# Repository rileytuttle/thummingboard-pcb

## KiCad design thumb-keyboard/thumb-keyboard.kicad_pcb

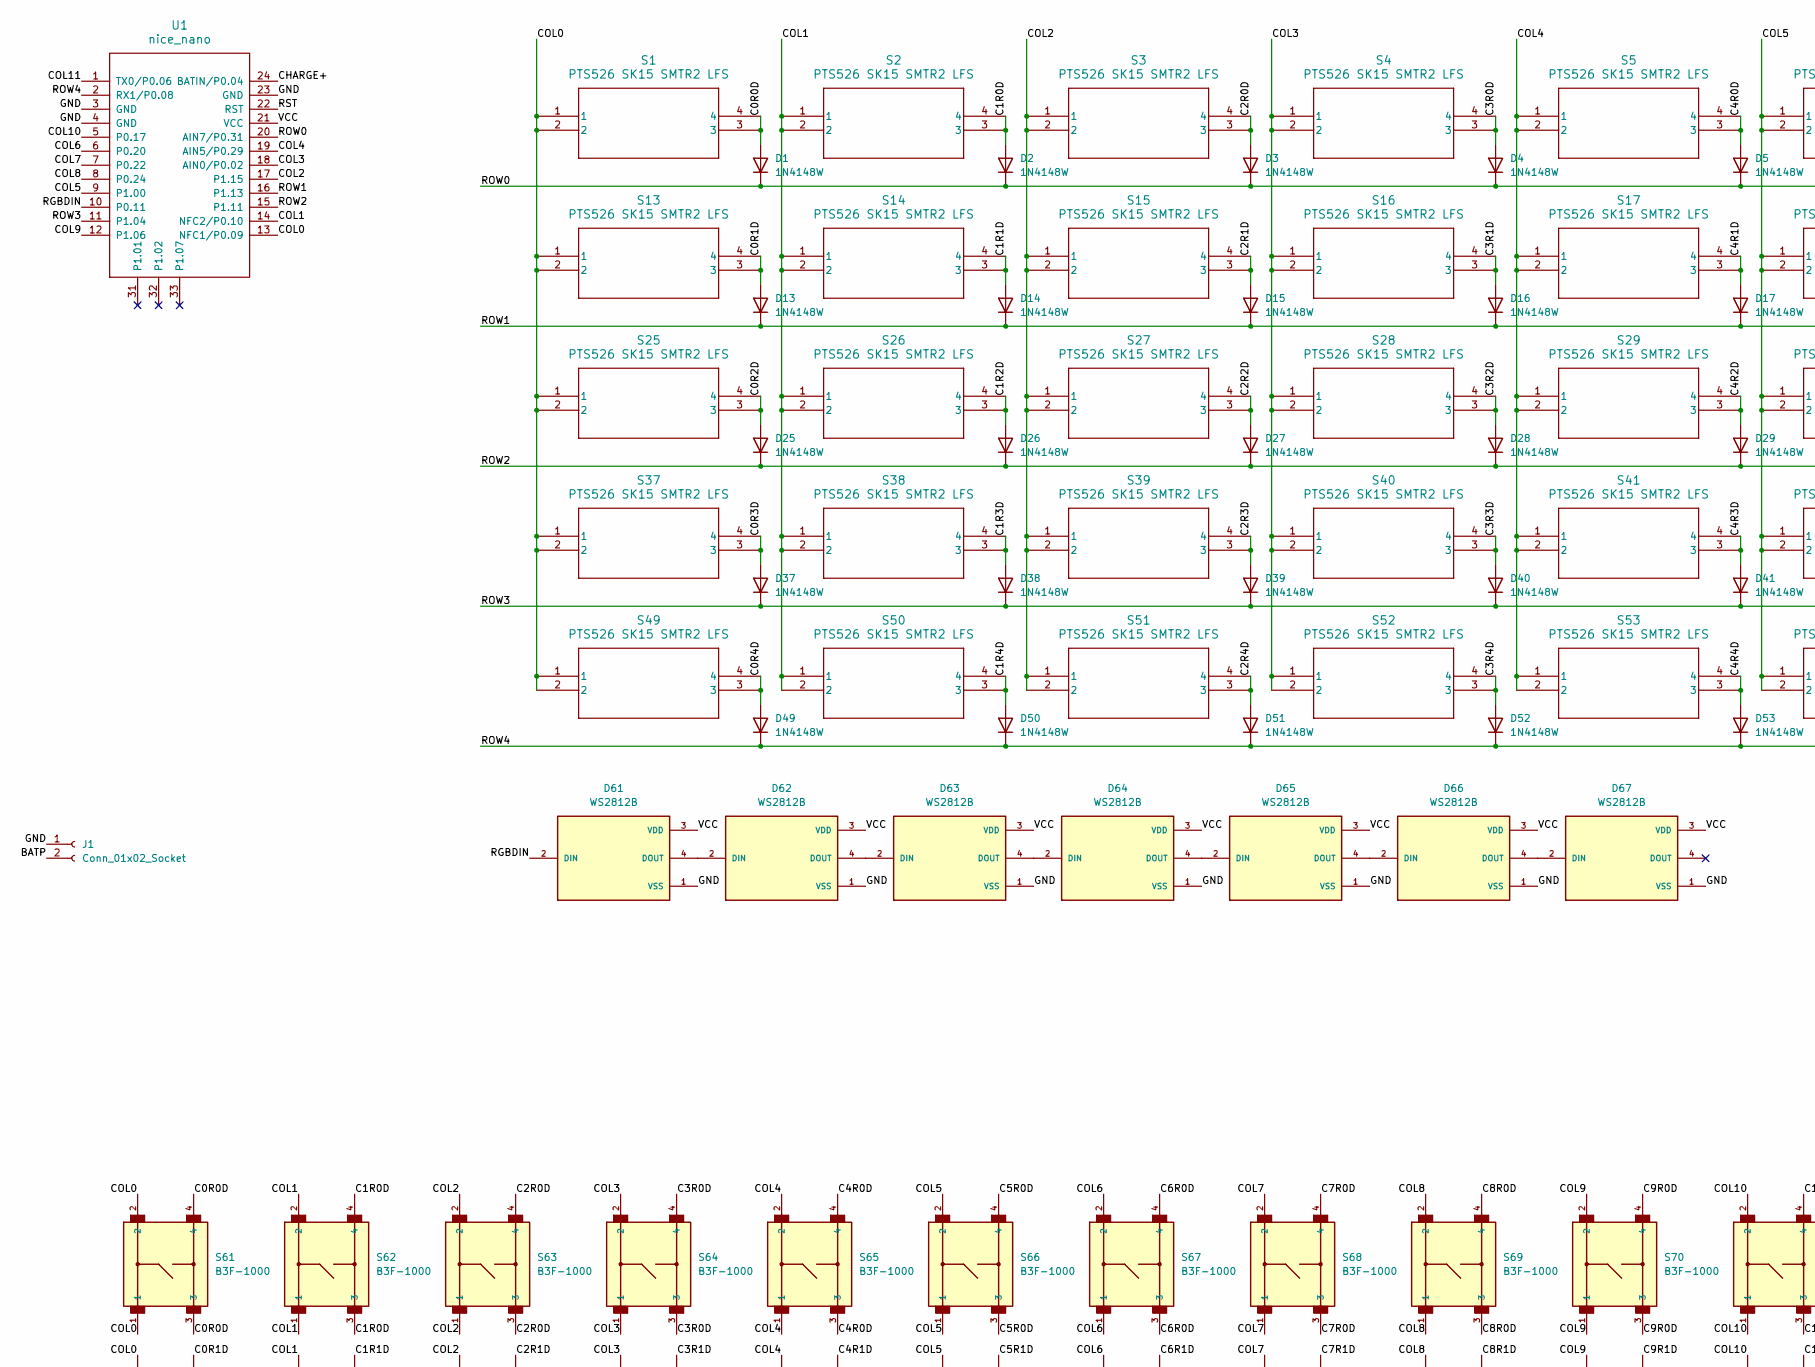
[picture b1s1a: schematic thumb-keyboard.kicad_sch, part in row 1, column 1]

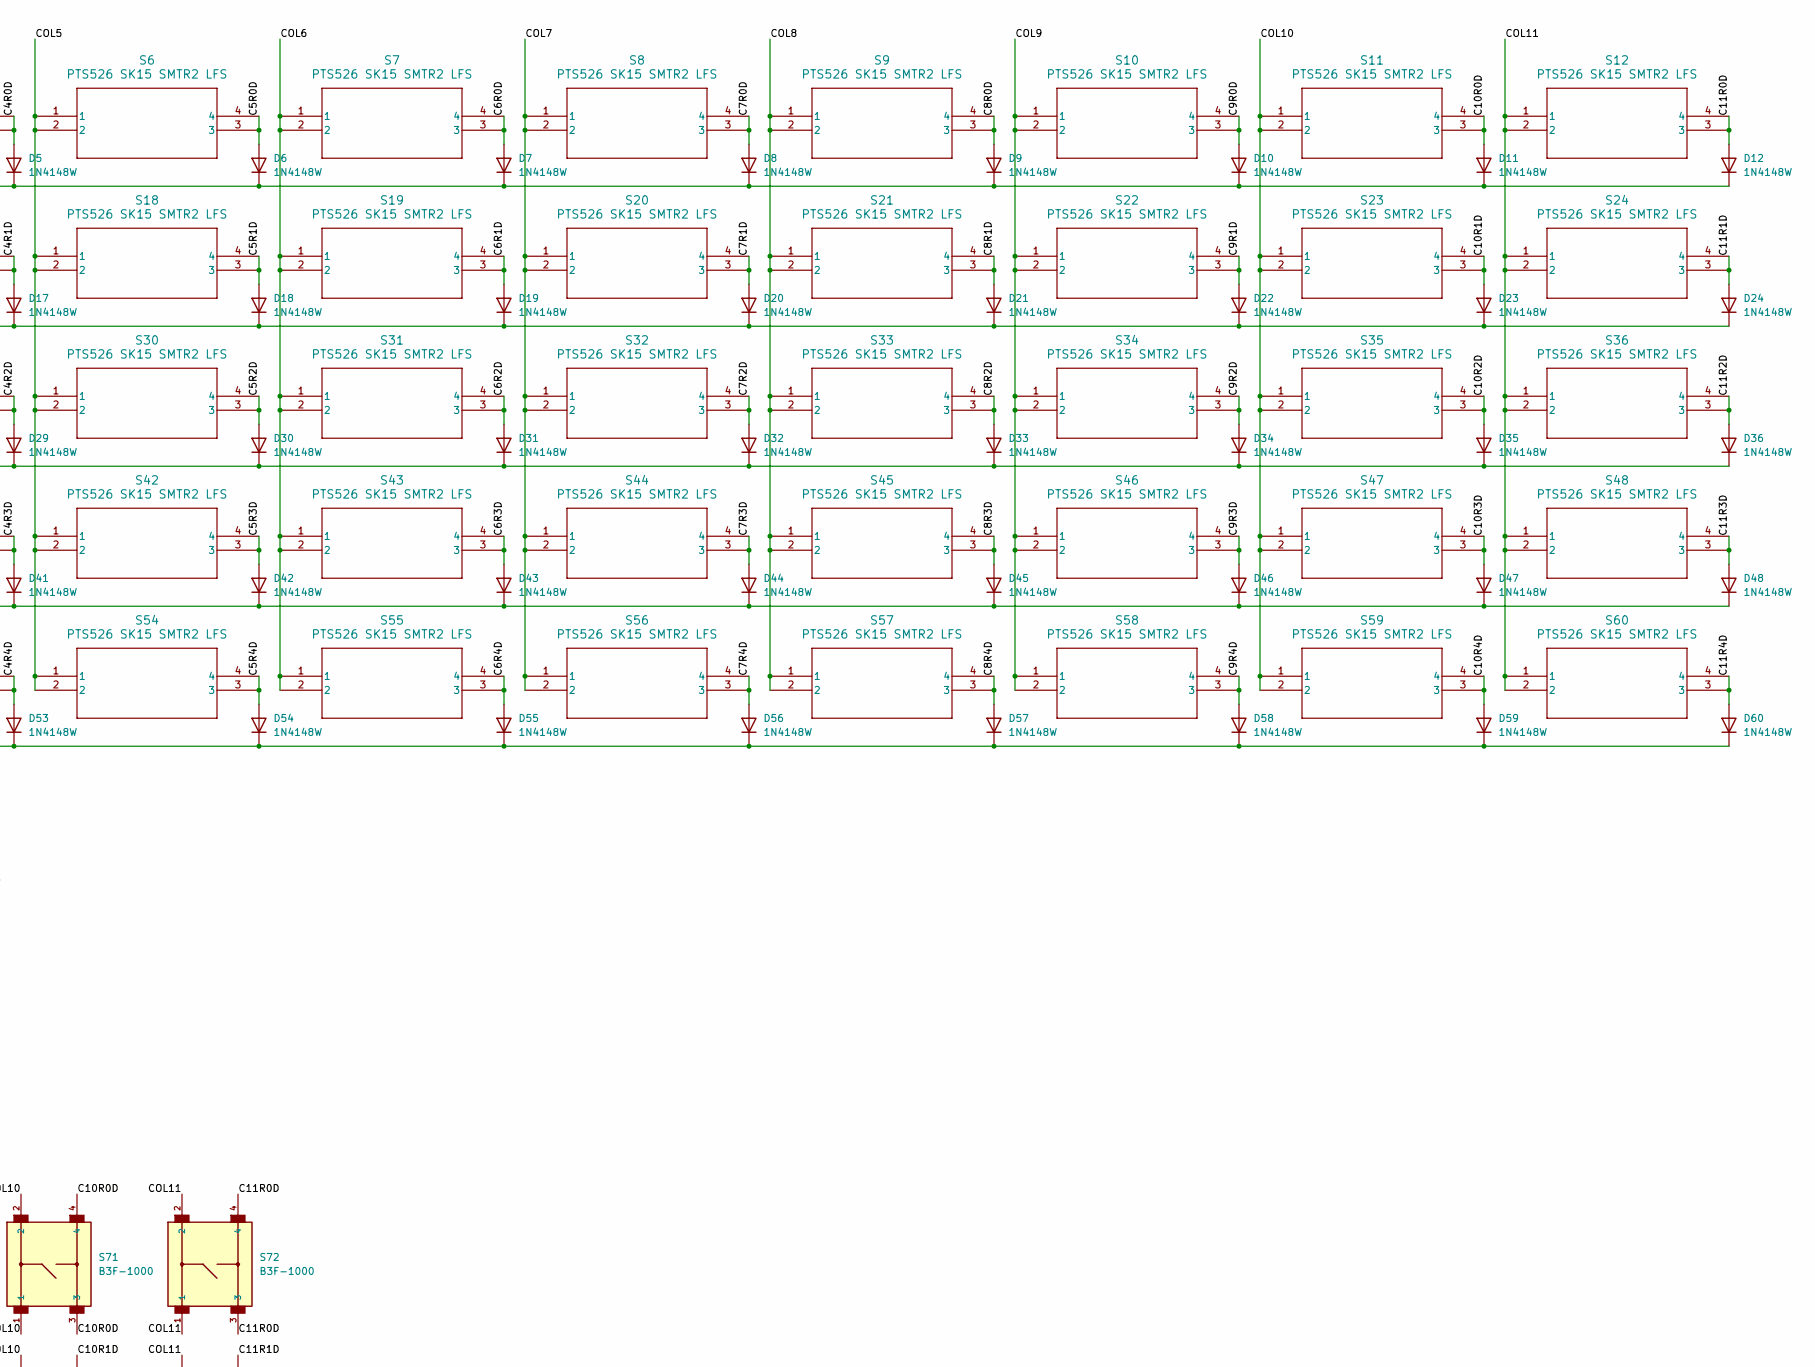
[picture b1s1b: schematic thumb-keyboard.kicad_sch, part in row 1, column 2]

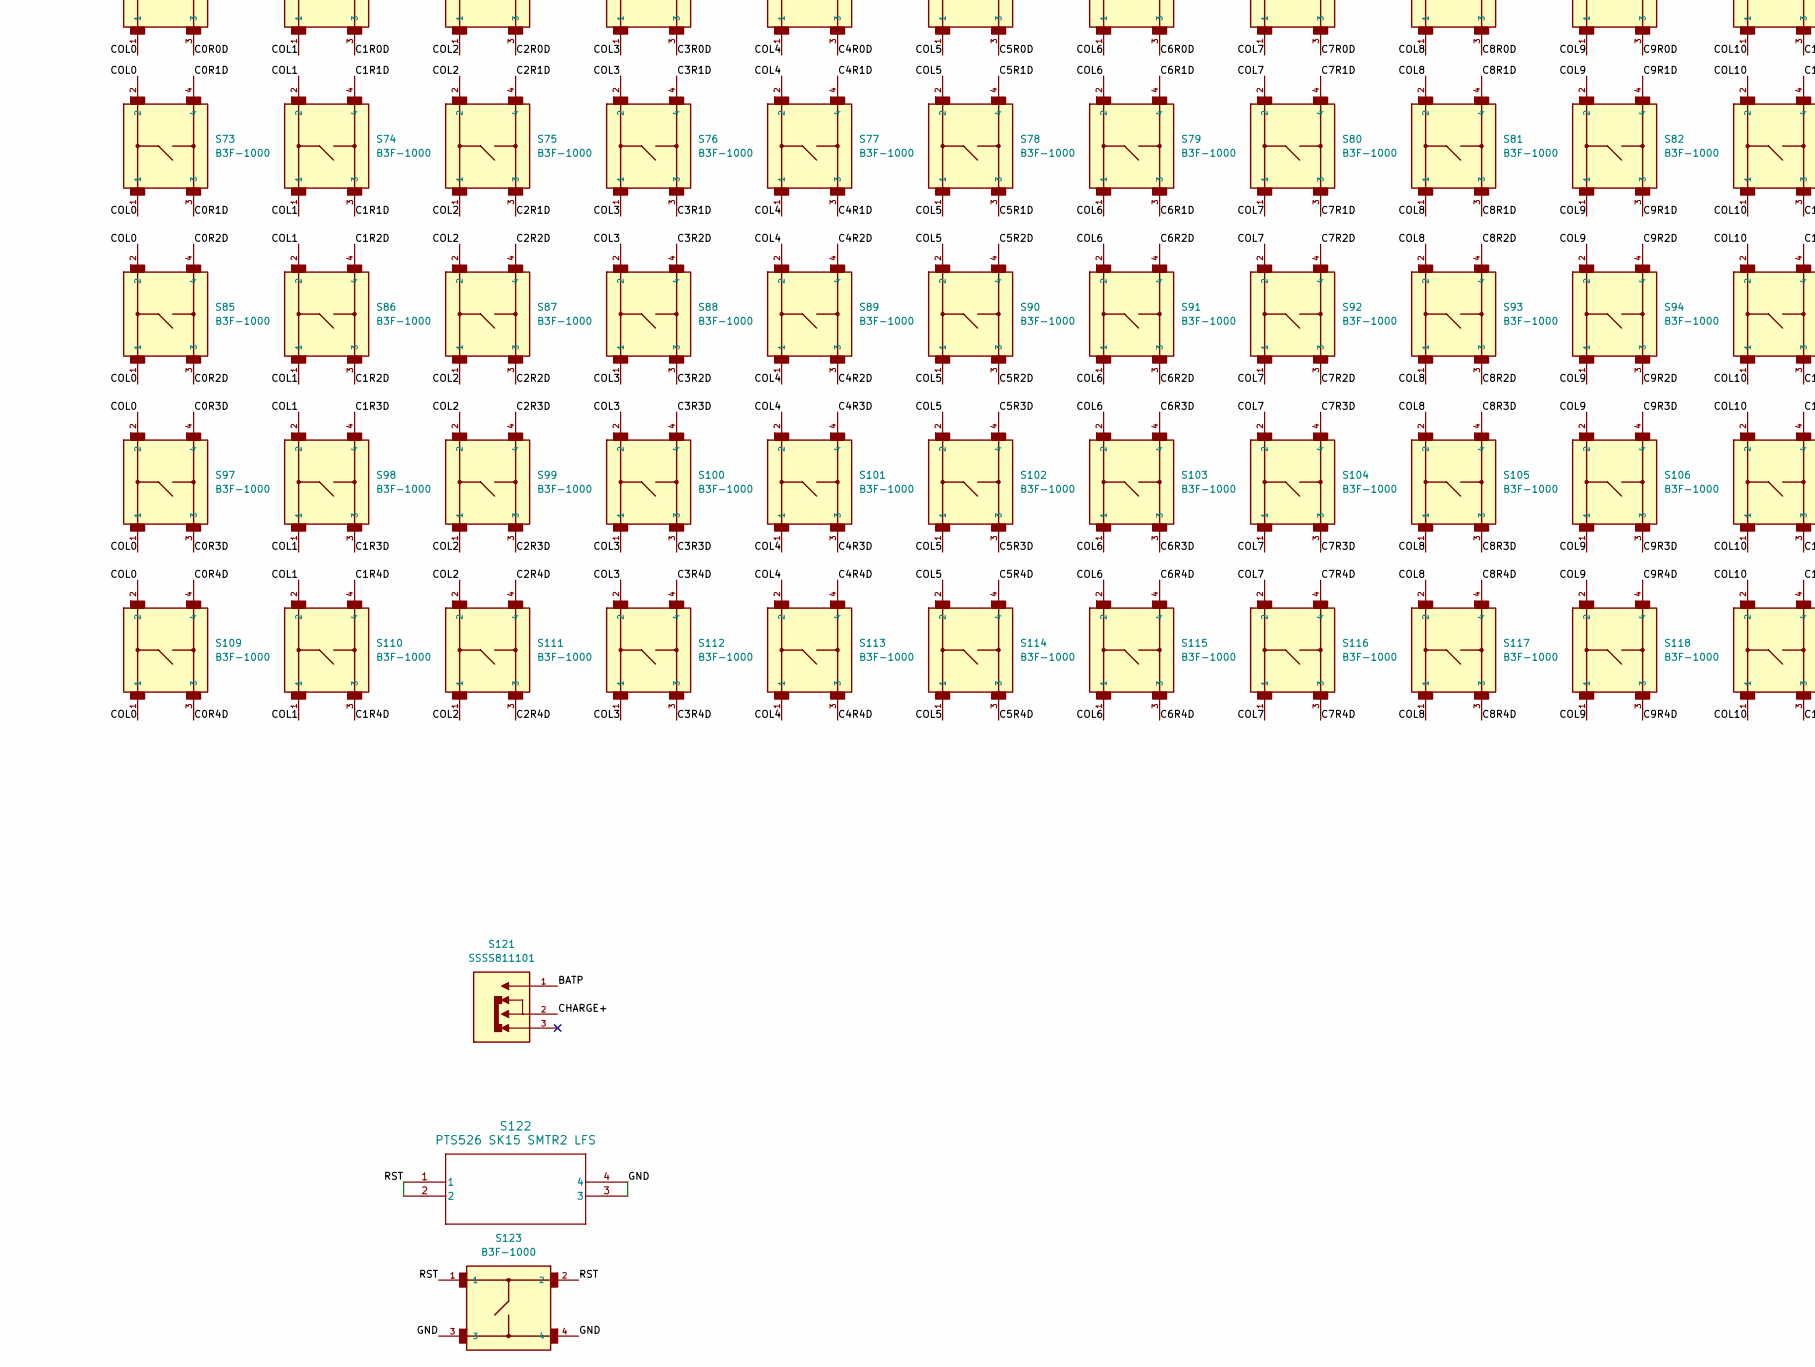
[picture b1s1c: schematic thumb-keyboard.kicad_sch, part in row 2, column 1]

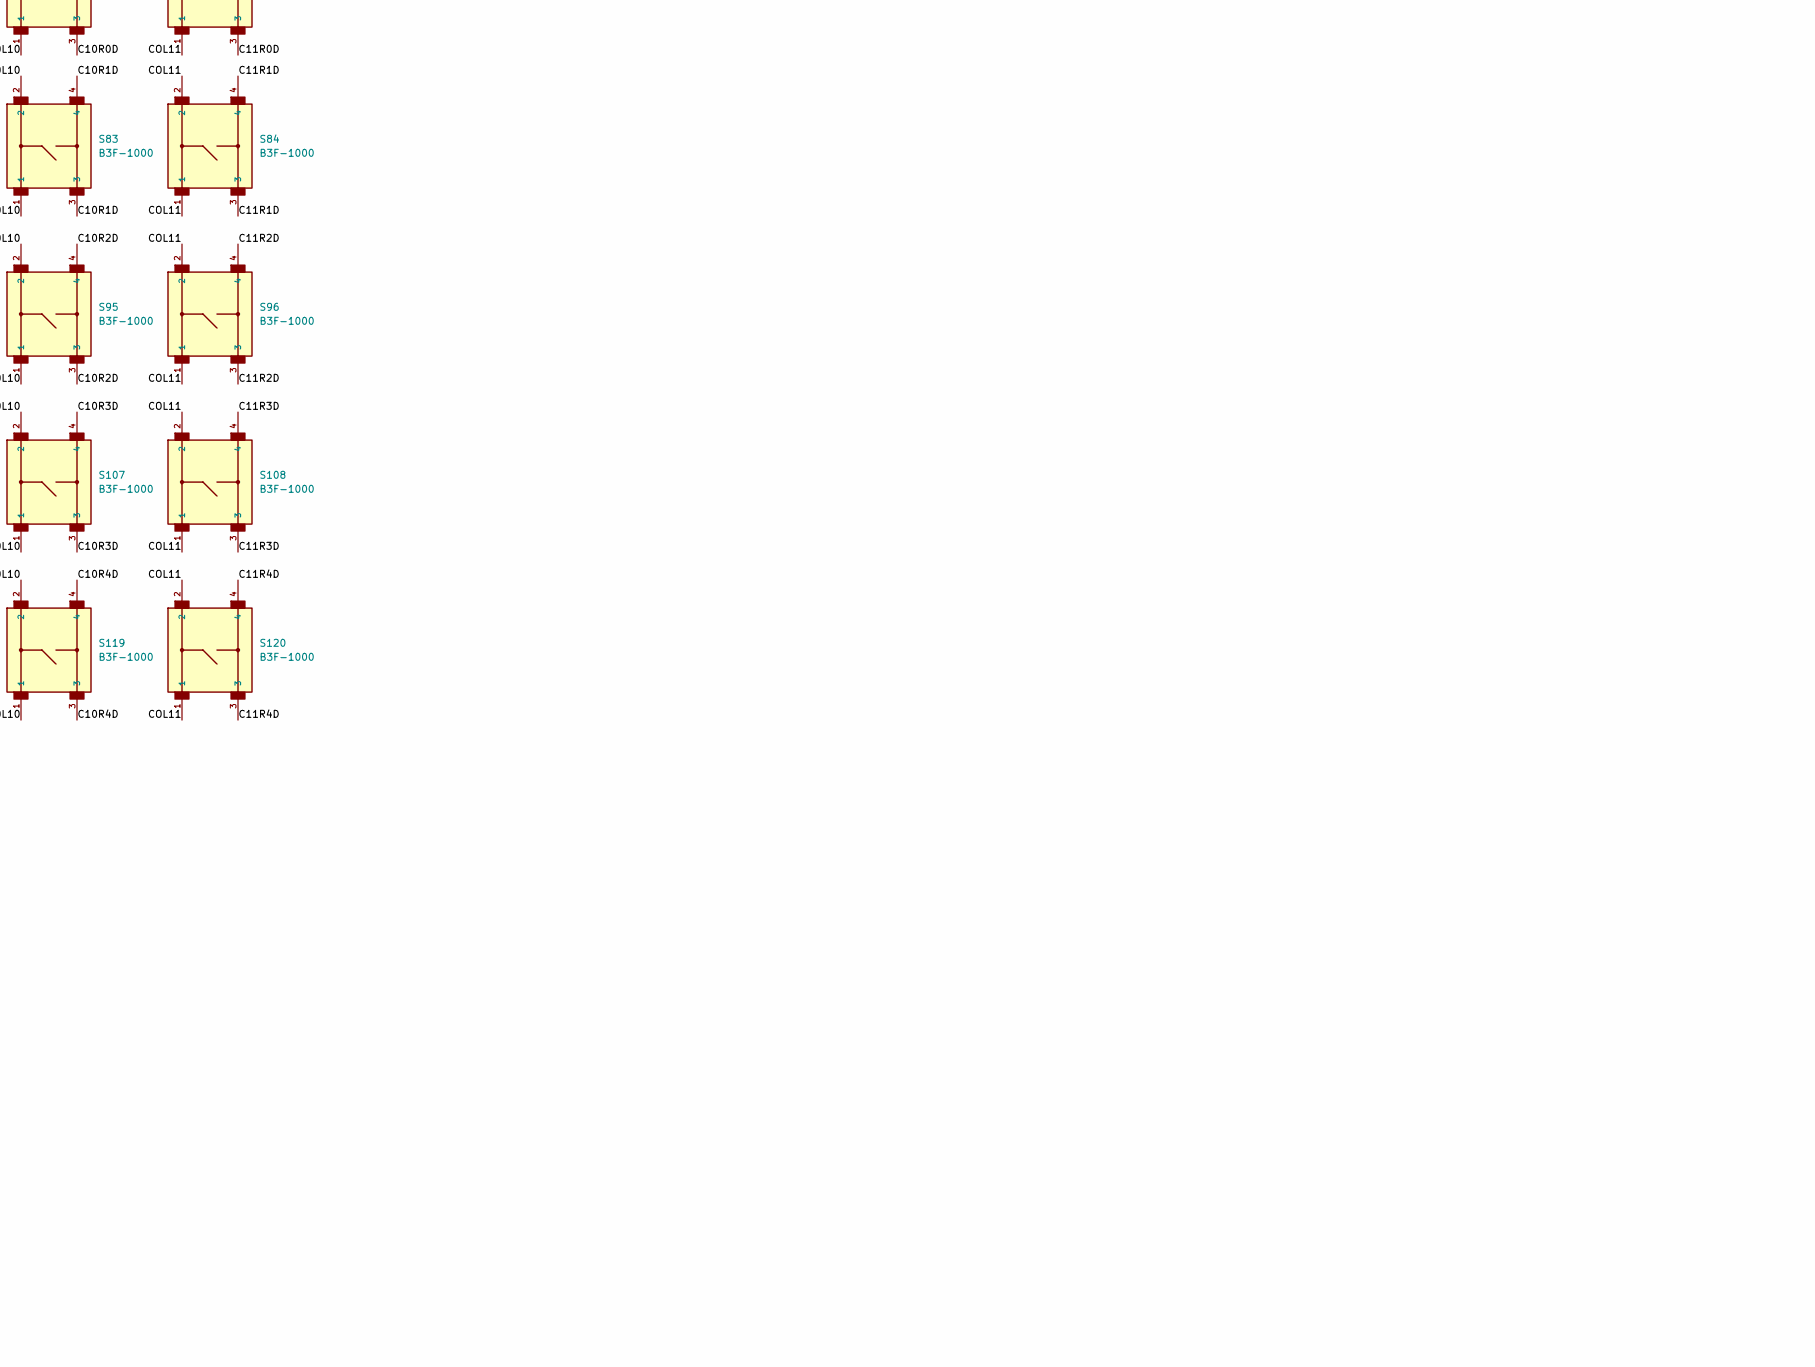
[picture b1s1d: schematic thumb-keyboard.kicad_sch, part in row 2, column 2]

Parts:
D1, D2, D3, D4, D5, D6, D7, D8, D9, D10, D11, D12, D13, D14, D15, D16, D17, D18, D19, D20, D21, D22, D23, D24, D25, D26, D27, D28, D29, D30, D31, D32, D33, D34, D35, D36, D37, D38, D39, D40, D41, D42, D43, D44, D45, D46, D47, D48, D49, D50, D51, D52, D53, D54, D55, D56, D57, D58, D59, D60: 1N4148W; D_SOD-123
D61, D62, D63, D64, D65, D66, D67: WS2812B; LED_1655; PARTREV 01
J1: Conn_01x02_Socket; JST_PH_S2B-PH-K_1x02_P2.00mm_Horizontal
S1, S2, S3, S4, S5, S6, S7, S8, S9, S10, S11, S12, S13, S14, S15, S16, S17, S18, S19, S20, S21, S22, S23, S24, S25, S26, S27, S28, S29, S30, S31, S32, S33, S34, S35, S36, S37, S38, S39, S40, S41, S42, S43, S44, S45, S46, S47, S48, S49, S50, S51, S52, S53, S54, S55, S56, S57, S58, S59, S60, S122: PTS526 SK15 SMTR2 LFS; SMT_FS
S61, S62, S63, S64, S65, S66, S67, S68, S69, S70, S71, S72, S73, S74, S75, S76, S77, S78, S79, S80, S81, S82, S83, S84, S85, S86, S87, S88, S89, S90, S91, S92, S93, S94, S95, S96, S97, S98, S99, S100, S101, S102, S103, S104, S105, S106, S107, S108, S109, S110, S111, S112, S113, S114, S115, S116, S117, S118, S119, S120, S123: B3F-1000; SW_B3F-1000
S121: SSSS811101; SW_SSSS811101; PARTREV N/A
U1: nice_nano

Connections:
/BATP: J1.2, S121.1; also elsewhere on the board
/C0R0D: D1.2 (A), S1.3, S1.4, S61.3, S61.4
/C0R1D: D13.2 (A), S13.3, S13.4, S73.3, S73.4
/C0R2D: D25.2 (A), S25.3, S25.4, S85.3, S85.4
/C0R3D: D37.2 (A), S37.3, S37.4, S97.3, S97.4
/C0R4D: D49.2 (A), S49.3, S49.4, S109.3, S109.4
/C1R0D: D2.2 (A), S2.3, S2.4, S62.3, S62.4
/C1R1D: D14.2 (A), S14.3, S14.4, S74.3, S74.4
/C1R2D: D26.2 (A), S26.3, S26.4, S86.3, S86.4
/C1R3D: D38.2 (A), S38.3, S38.4, S98.3, S98.4
/C1R4D: D50.2 (A), S50.3, S50.4, S110.3, S110.4
/C2R0D: D3.2 (A), S3.3, S3.4, S63.3, S63.4
/C2R1D: D15.2 (A), S15.3, S15.4, S75.3, S75.4
/C2R2D: D27.2 (A), S27.3, S27.4, S87.3, S87.4
/C2R3D: D39.2 (A), S39.3, S39.4, S99.3, S99.4
/C2R4D: D51.2 (A), S51.3, S51.4, S111.3, S111.4
/C3R0D: D4.2 (A), S4.3, S4.4, S64.3, S64.4
/C3R1D: D16.2 (A), S16.3, S16.4, S76.3, S76.4
/C3R2D: D28.2 (A), S28.3, S28.4, S88.3, S88.4
/C3R3D: D40.2 (A), S40.3, S40.4, S100.3, S100.4
/C3R4D: D52.2 (A), S52.3, S52.4, S112.3, S112.4
/C4R0D: D5.2 (A), S5.3, S5.4, S65.3, S65.4
/C4R1D: D17.2 (A), S17.3, S17.4, S77.3, S77.4
/C4R2D: D29.2 (A), S29.3, S29.4, S89.3, S89.4
/C4R3D: D41.2 (A), S41.3, S41.4, S101.3, S101.4
/C4R4D: D53.2 (A), S53.3, S53.4, S113.3, S113.4
/C5R0D: D6.2 (A), S6.3, S6.4, S66.3, S66.4
/C5R1D: D18.2 (A), S18.3, S18.4, S78.3, S78.4
/C5R2D: D30.2 (A), S30.3, S30.4, S90.3, S90.4
/C5R3D: D42.2 (A), S42.3, S42.4, S102.3, S102.4
/C5R4D: D54.2 (A), S54.3, S54.4, S114.3, S114.4
/C6R0D: D7.2 (A), S7.3, S7.4, S67.3, S67.4
/C6R1D: D19.2 (A), S19.3, S19.4, S79.3, S79.4
/C6R2D: D31.2 (A), S31.3, S31.4, S91.3, S91.4
/C6R3D: D43.2 (A), S43.3, S43.4, S103.3, S103.4
/C6R4D: D55.2 (A), S55.3, S55.4, S115.3, S115.4
/C7R0D: D8.2 (A), S8.3, S8.4, S68.3, S68.4
/C7R1D: D20.2 (A), S20.3, S20.4, S80.3, S80.4
/C7R2D: D32.2 (A), S32.3, S32.4, S92.3, S92.4
/C7R3D: D44.2 (A), S44.3, S44.4, S104.3, S104.4
/C7R4D: D56.2 (A), S56.3, S56.4, S116.3, S116.4
/C8R0D: D9.2 (A), S9.3, S9.4, S69.3, S69.4
/C8R1D: D21.2 (A), S21.3, S21.4, S81.3, S81.4
/C8R2D: D33.2 (A), S33.3, S33.4, S93.3, S93.4
/C8R3D: D45.2 (A), S45.3, S45.4, S105.3, S105.4
/C8R4D: D57.2 (A), S57.3, S57.4, S117.3, S117.4
/C9R0D: D10.2 (A), S10.3, S10.4, S70.3, S70.4
/C9R1D: D22.2 (A), S22.3, S22.4, S82.3, S82.4
/C9R2D: D34.2 (A), S34.3, S34.4, S94.3, S94.4
/C9R3D: D46.2 (A), S46.3, S46.4, S106.3, S106.4
/C9R4D: D58.2 (A), S58.3, S58.4, S118.3, S118.4
/C10R0D: D11.2 (A), S11.3, S11.4, S71.3, S71.4
/C10R1D: D23.2 (A), S23.3, S23.4, S83.3, S83.4
/C10R2D: D35.2 (A), S35.3, S35.4, S95.3, S95.4
/C10R3D: D47.2 (A), S47.3, S47.4, S107.3, S107.4
/C10R4D: D59.2 (A), S59.3, S59.4, S119.3, S119.4
/C11R0D: D12.2 (A), S12.3, S12.4, S72.3, S72.4
/C11R1D: D24.2 (A), S24.3, S24.4, S84.3, S84.4
/C11R2D: D36.2 (A), S36.3, S36.4, S96.3, S96.4
/C11R3D: D48.2 (A), S48.3, S48.4, S108.3, S108.4
/C11R4D: D60.2 (A), S60.3, S60.4, S120.3, S120.4
/CHARGE+: S121.2, U1.24 (BATIN/P0.04)
/COL0: S1.1, S1.2, S13.1, S13.2, S25.1, S25.2, S37.1, S37.2, S49.1, S49.2, S61.1, S61.2, S73.1, S73.2, S85.1, S85.2, S97.1, S97.2, S109.1, S109.2, U1.13 (NFC1/P0.09)
/COL1: S2.1, S2.2, S14.1, S14.2, S26.1, S26.2, S38.1, S38.2, S50.1, S50.2, S62.1, S62.2, S74.1, S74.2, S86.1, S86.2, S98.1, S98.2, S110.1, S110.2, U1.14 (NFC2/P0.10)
/COL2: S3.1, S3.2, S15.1, S15.2, S27.1, S27.2, S39.1, S39.2, S51.1, S51.2, S63.1, S63.2, S75.1, S75.2, S87.1, S87.2, S99.1, S99.2, S111.1, S111.2, U1.17 (P1.15)
/COL3: S4.1, S4.2, S16.1, S16.2, S28.1, S28.2, S40.1, S40.2, S52.1, S52.2, S64.1, S64.2, S76.1, S76.2, S88.1, S88.2, S100.1, S100.2, S112.1, S112.2, U1.18 (AIN0/P0.02)
/COL4: S5.1, S5.2, S17.1, S17.2, S29.1, S29.2, S41.1, S41.2, S53.1, S53.2, S65.1, S65.2, S77.1, S77.2, S89.1, S89.2, S101.1, S101.2, S113.1, S113.2, U1.19 (AIN5/P0.29)
/COL5: S6.1, S6.2, S18.1, S18.2, S30.1, S30.2, S42.1, S42.2, S54.1, S54.2, S66.1, S66.2, S78.1, S78.2, S90.1, S90.2, S102.1, S102.2, S114.1, S114.2, U1.9 (P1.00)
/COL6: S7.1, S7.2, S19.1, S19.2, S31.1, S31.2, S43.1, S43.2, S55.1, S55.2, S67.1, S67.2, S79.1, S79.2, S91.1, S91.2, S103.1, S103.2, S115.1, S115.2, U1.6 (P0.20)
/COL7: S8.1, S8.2, S20.1, S20.2, S32.1, S32.2, S44.1, S44.2, S56.1, S56.2, S68.1, S68.2, S80.1, S80.2, S92.1, S92.2, S104.1, S104.2, S116.1, S116.2, U1.7 (P0.22)
/COL8: S9.1, S9.2, S21.1, S21.2, S33.1, S33.2, S45.1, S45.2, S57.1, S57.2, S69.1, S69.2, S81.1, S81.2, S93.1, S93.2, S105.1, S105.2, S117.1, S117.2, U1.8 (P0.24)
/COL9: S10.1, S10.2, S22.1, S22.2, S34.1, S34.2, S46.1, S46.2, S58.1, S58.2, S70.1, S70.2, S82.1, S82.2, S94.1, S94.2, S106.1, S106.2, S118.1, S118.2, U1.12 (P1.06)
/COL10: S11.1, S11.2, S23.1, S23.2, S35.1, S35.2, S47.1, S47.2, S59.1, S59.2, S71.1, S71.2, S83.1, S83.2, S95.1, S95.2, S107.1, S107.2, S119.1, S119.2, U1.5 (P0.17)
/COL11: S12.1, S12.2, S24.1, S24.2, S36.1, S36.2, S48.1, S48.2, S60.1, S60.2, S72.1, S72.2, S84.1, S84.2, S96.1, S96.2, S108.1, S108.2, S120.1, S120.2, U1.1 (TX0/P0.06)
/GND: D61.1 (VSS), D62.1 (VSS), D63.1 (VSS), D64.1 (VSS), D65.1 (VSS), D66.1 (VSS), D67.1 (VSS), J1.1, S122.3, S122.4, S123.3, S123.4, U1.3 (GND), U1.4 (GND), U1.23 (GND); also elsewhere on the board
/RGBDIN: D61.2 (DIN), U1.10 (P0.11); also elsewhere on the board
/ROW0: D1.1 (K), D2.1 (K), D3.1 (K), D4.1 (K), D5.1 (K), D6.1 (K), D7.1 (K), D8.1 (K), D9.1 (K), D10.1 (K), D11.1 (K), D12.1 (K), U1.20 (AIN7/P0.31)
/ROW1: D13.1 (K), D14.1 (K), D15.1 (K), D16.1 (K), D17.1 (K), D18.1 (K), D19.1 (K), D20.1 (K), D21.1 (K), D22.1 (K), D23.1 (K), D24.1 (K), U1.16 (P1.13)
/ROW2: D25.1 (K), D26.1 (K), D27.1 (K), D28.1 (K), D29.1 (K), D30.1 (K), D31.1 (K), D32.1 (K), D33.1 (K), D34.1 (K), D35.1 (K), D36.1 (K), U1.15 (P1.11)
/ROW3: D37.1 (K), D38.1 (K), D39.1 (K), D40.1 (K), D41.1 (K), D42.1 (K), D43.1 (K), D44.1 (K), D45.1 (K), D46.1 (K), D47.1 (K), D48.1 (K), U1.11 (P1.04)
/ROW4: D49.1 (K), D50.1 (K), D51.1 (K), D52.1 (K), D53.1 (K), D54.1 (K), D55.1 (K), D56.1 (K), D57.1 (K), D58.1 (K), D59.1 (K), D60.1 (K), U1.2 (RX1/P0.08)
/RST: S122.1, S122.2, S123.1, S123.2, U1.22 (RST)
/VCC: D61.3 (VDD), D62.3 (VDD), D63.3 (VDD), D64.3 (VDD), D65.3 (VDD), D66.3 (VDD), D67.3 (VDD), U1.21 (VCC)
unnamed: D61.4 (DOUT), D62.2 (DIN)
unnamed: D62.4 (DOUT), D63.2 (DIN)
unnamed: D63.4 (DOUT), D64.2 (DIN)
unnamed 86: D64.4 (DOUT), D65.2 (DIN); also elsewhere on the board
unnamed: D65.4 (DOUT), D66.2 (DIN)
unnamed: D66.4 (DOUT), D67.2 (DIN)

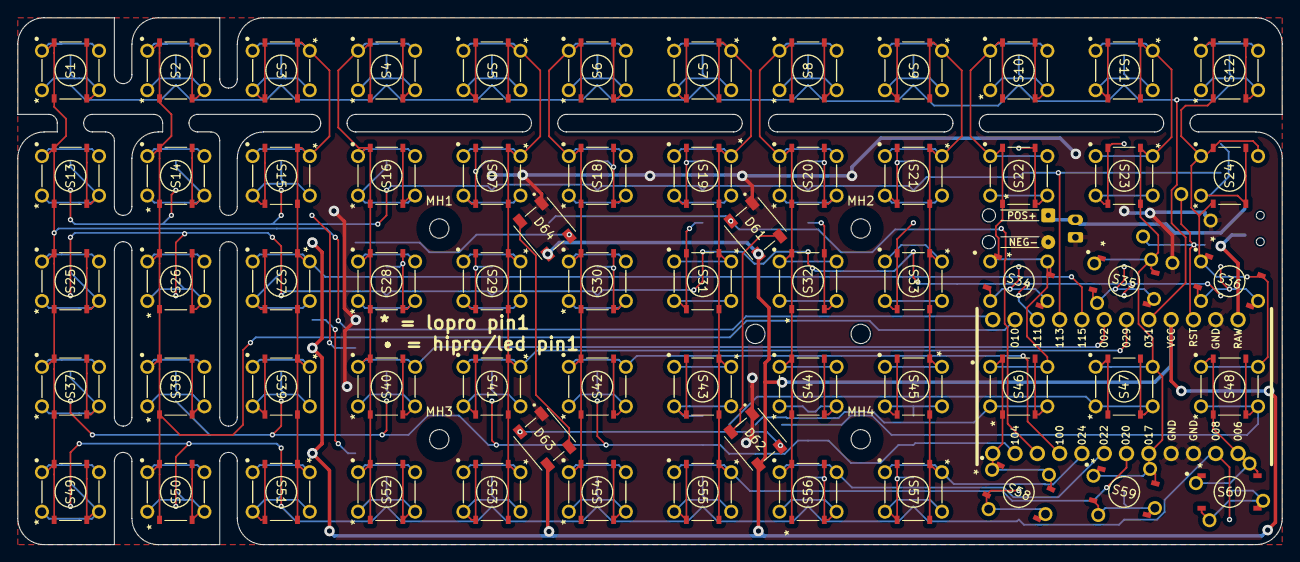
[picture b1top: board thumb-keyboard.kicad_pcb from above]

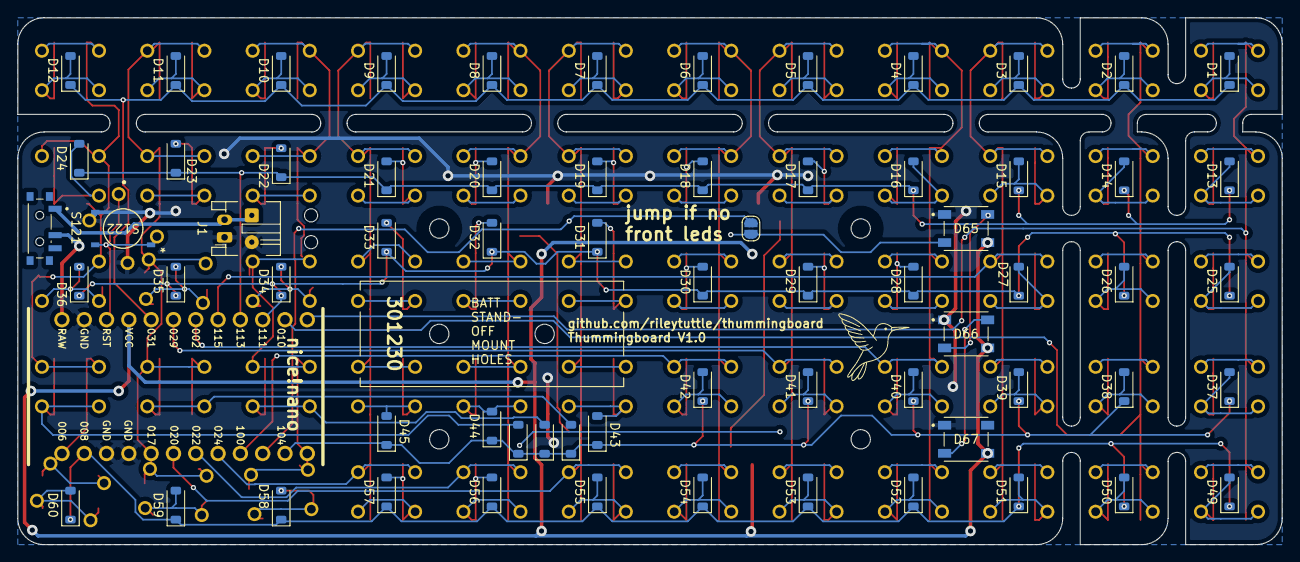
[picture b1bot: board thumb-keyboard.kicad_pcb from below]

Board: 2 copper layers, 144.0 x 60.0 mm, 199 parts (69 on the bottom side), 89 nets.

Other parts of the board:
BATT STANDOFF: MountingHole_2.2mm_M2
GND - POS: SolderWire-0.1sqmm_1x02_P3.6mm_D0.4mm_OD1mm_Relief
JumpIfNoFrontLED: SolderJumper-2_P1.3mm_Open_RoundedPad1.0x1.5mm
MH1, MH2, MH3, MH4: MountingHole_2.2mm_M2

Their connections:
/BATP: GND - POS.1; also elsewhere on the board
/GND: GND - POS.2; also elsewhere on the board
/RGBDIN: JumpIfNoFrontLED.2; also elsewhere on the board
unnamed 86: JumpIfNoFrontLED.1; also elsewhere on the board

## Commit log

2025-08-27 Added ws2812b leds to thumb keyboard. they may be too tall. I may have to switch to the 222AMVBAR tactile switches and space everything out like a centimeter more. that would be a lot of work but wou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
2025-08-27 going to try reducing the slot diam
2025-08-27 adding the thumb keyboard to this repo for now to share the libraries but really I should move to its own repo. I will do that another time
2025-09-05 working on different switches. last commit before adding the B3F-1000 switch option and extending the x gap from 10 - 12 mm
2025-09-05 first commit after change to branch with optional B3F-1000 switches. footprint is going to be 144x60
2025-09-05 have something that looks alright. max size of 144x60mm. A little concerning how messy it is though
2025-09-05 sent out v1.0 pcb order
2025-09-05 finishing migrating to thummingboard repo
2025-09-16 adding gitignore
2026-02-13 small maintenence
